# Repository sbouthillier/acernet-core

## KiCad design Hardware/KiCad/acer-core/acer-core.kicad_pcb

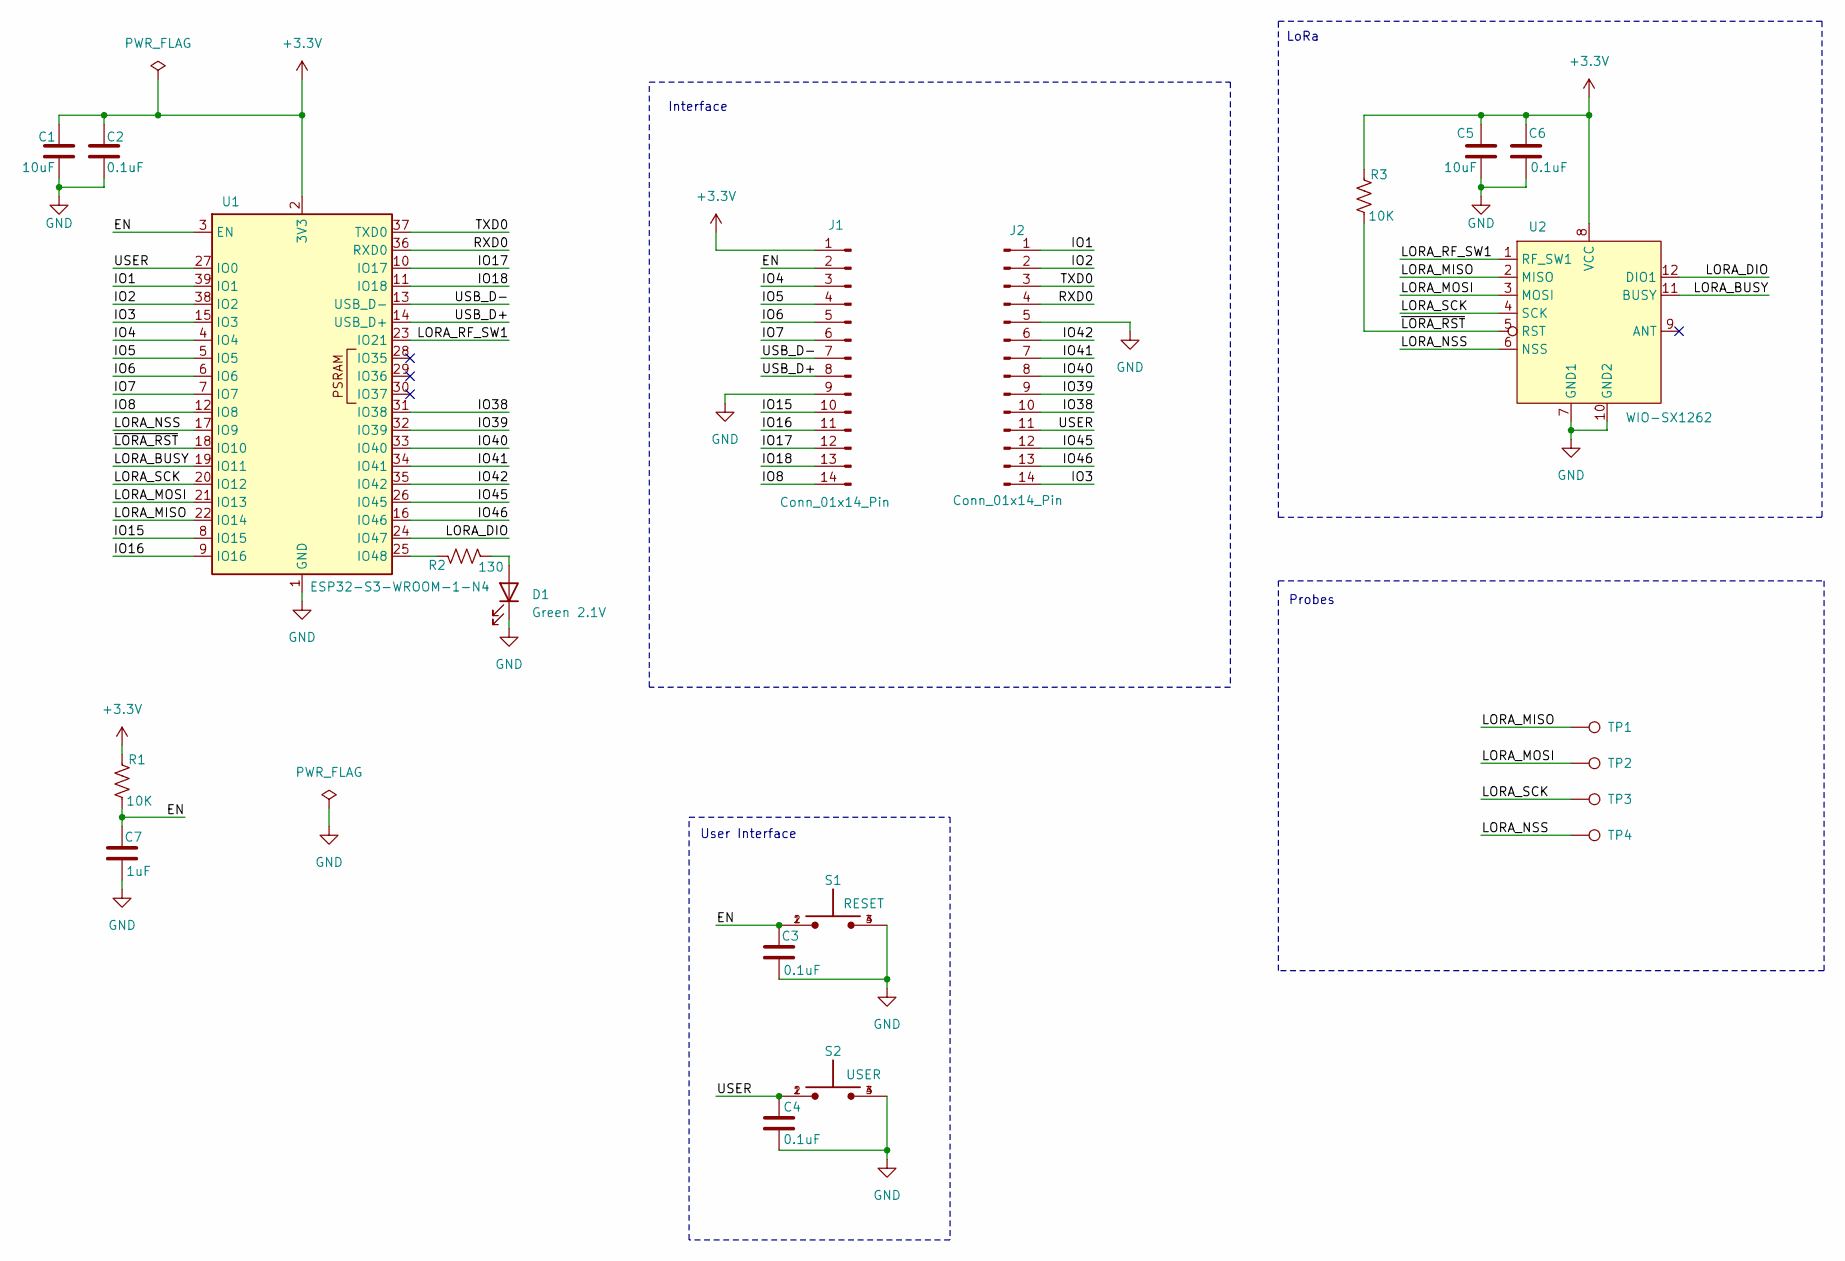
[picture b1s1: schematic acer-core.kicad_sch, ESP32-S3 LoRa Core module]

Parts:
C1, C5: 10uF; C_0805_2012Metric; MPN GRM21BR71A106KA73L
C2, C3, C4, C6: 0.1uF; C_0603_1608Metric; MPN CL10B104JB8NNNC
C7: 1uF; C_0603_1608Metric; MPN CL10B104JB8NNNC
D1: Green 2.1V; LED_0603_1608Metric; MPN LTST-C190GKT
J1, J2: Conn_01x14_Pin; PinHeader_1x14_P2.54mm_Vertical
R1, R3: 10K; R_0603_1608Metric; MPN CRCW060310K0FKEA
R2: 130; R_0603_1608Metric; MPN RC0603FR-07130RL
S1: RESET; SW_SKRPABE010; MPN SKRPABE010
S2: USER; SW_SKRPABE010; MPN SKRPABE010
TP1, TP2, TP3, TP4: TestPoint; TestPoint_Pad_D1.5mm
U1: ESP32-S3-WROOM-1-N4; ESP32-S3-WROOM-1; MPN ESP32-S3-WROOM-1-N4
U2: WIO-SX1262; Wio-SX1262-SB; MPN 114993390

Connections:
+3.3V: C1.1, C2.1, C5.1, C6.1, J1.1, R1.2, R3.2, U1.2 (3V3), U2.8 (VCC)
/EN: C3.1, C7.1, J1.2, R1.1, S1.1, S1.2, U1.3 (EN)
/IO1: J2.1, U1.39 (IO1)
/IO2: J2.2, U1.38 (IO2)
/IO3: J2.14, U1.15 (IO3)
/IO4: J1.3, U1.4 (IO4)
/IO5: J1.4, U1.5 (IO5)
/IO6: J1.5, U1.6 (IO6)
/IO7: J1.6, U1.7 (IO7)
/IO8: J1.14, U1.12 (IO8)
/IO15: J1.10, U1.8 (IO15)
/IO16: J1.11, U1.9 (IO16)
/IO17: J1.12, U1.10 (IO17)
/IO18: J1.13, U1.11 (IO18)
/IO38: J2.10, U1.31 (IO38)
/IO39: J2.9, U1.32 (IO39)
/IO40: J2.8, U1.33 (IO40)
/IO41: J2.7, U1.34 (IO41)
/IO42: J2.6, U1.35 (IO42)
/IO45: J2.12, U1.26 (IO45)
/IO46: J2.13, U1.16 (IO46)
/LORA_BUSY: U1.19 (IO11), U2.11 (BUSY)
/LORA_DIO: U1.24 (IO47), U2.12 (DIO1)
/LORA_MISO: TP1.1 (1_1), U1.22 (IO14), U2.2 (MISO)
/LORA_MOSI: TP2.1 (1_1), U1.21 (IO13), U2.3 (MOSI)
/LORA_NSS: TP4.1 (1_1), U1.17 (IO9), U2.6 (NSS)
/LORA_RF_SW1: U1.23 (IO21), U2.1 (RF_SW1)
/LORA_SCK: TP3.1 (1_1), U1.20 (IO12), U2.4 (SCK)
/RXD0: J2.4, U1.36 (RXD0)
/TXD0: J2.3, U1.37 (TXD0)
/USB_D+: J1.8, U1.14 (USB_D+)
/USB_D-: J1.7, U1.13 (USB_D-)
/USER: C4.1, J2.11, S2.1, S2.2, U1.27 (IO0)
/~LORA_RST: R3.1, U1.18 (IO10), U2.5 (RST)
GND: C1.2, C2.2, C3.2, C4.2, C5.2, C6.2, C7.2, D1.1 (K), J1.9, J2.5, S1.3, S1.4, S2.3, S2.4, U1.1 (GND), U1.40 (GND), U1.41 (GND), U2.7 (GND1), U2.10 (GND2)
unnamed: D1.2 (A), R2.1
unnamed: R2.2, U1.25 (IO48)

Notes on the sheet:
User Interface
LoRa
Interface
Probes

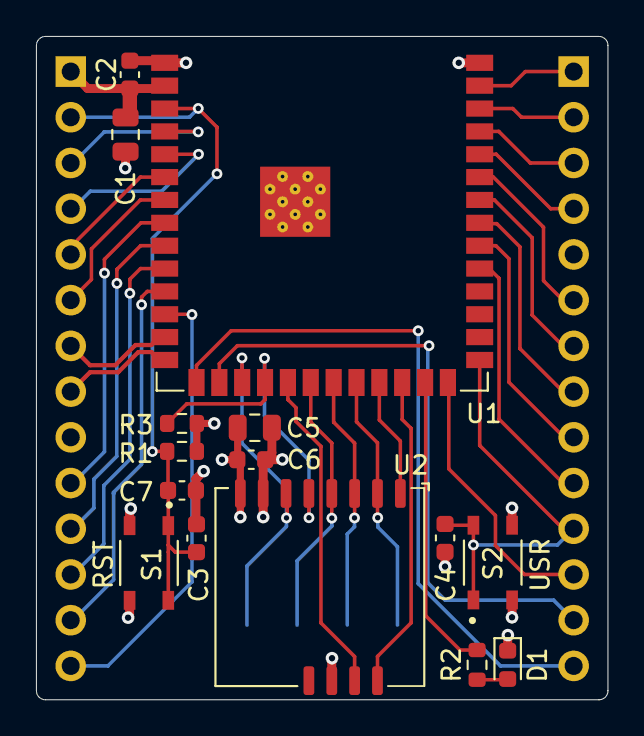
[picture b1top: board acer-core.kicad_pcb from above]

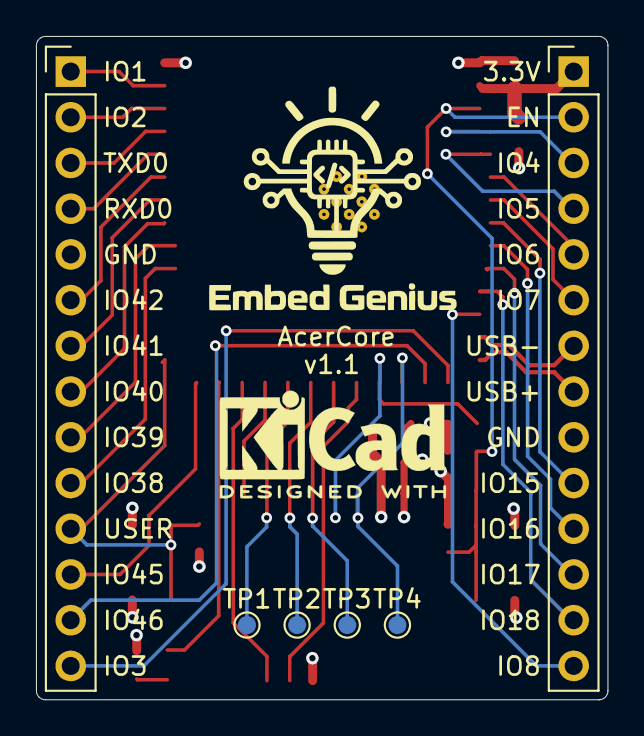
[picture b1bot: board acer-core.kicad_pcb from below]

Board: 4 copper layers, 31.8 x 36.9 mm, 21 parts (6 on the bottom side), 37 nets.

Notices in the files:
Hardware/KiCad/acer-core/acer-core.kicad_pcb:
License CC BY-SA
